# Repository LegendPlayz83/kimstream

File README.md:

# kimstream
This is my Macropad design, which I made from scratch. It has an open top to show to cool pcb designs

# Specifications
 
<ul>
<li>6x Cherry MX Switches <br>
<li>1x XIAO RP2040 <br>
<li>6x Blank DSA Keycaps <br>
<li>4x M3x16 Bolt <br>
<li>4x M3 Heatset <br>
<li>1x EC11 Rotary Encoder</li>  
</ul>

Others:
<ul>
<li>KMK Firmware
<li>Bottom Case.stl
</ul>

<h3>Schematic-</h3>

<h3>PCB</h3>

<h3>Case</h3>

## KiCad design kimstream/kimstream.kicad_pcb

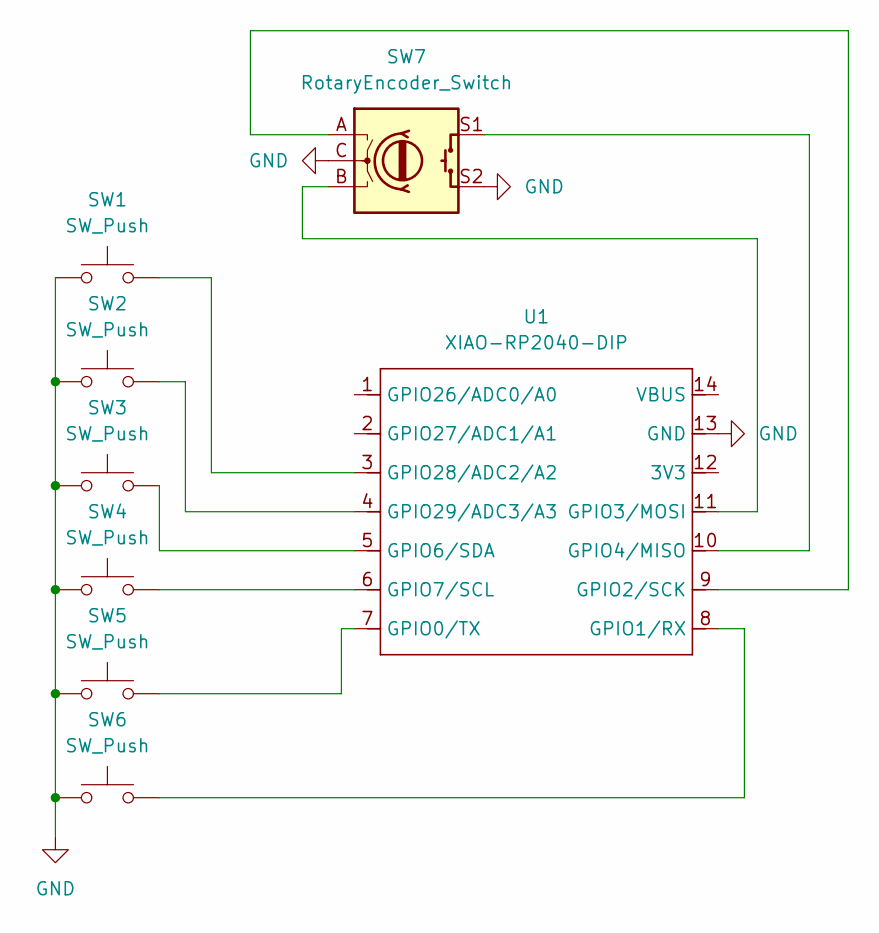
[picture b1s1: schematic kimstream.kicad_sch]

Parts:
SW1, SW2, SW3, SW4, SW5, SW6: SW_Push; SW_Cherry_MX_1.00u_PCB
SW7: RotaryEncoder_Switch; RotaryEncoder_Alps_EC11E-Switch_Vertical_H20mm
U1: XIAO-RP2040-DIP

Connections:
GND: SW1.1, SW2.1, SW3.1, SW4.1, SW5.1, SW6.1, SW7.C, SW7.S2, U1.13 (GND)
unnamed: SW5.2, U1.7 (GPIO0/TX)
unnamed: SW6.2, U1.8 (GPIO1/RX)
unnamed: SW7.A, U1.9 (GPIO2/SCK)
unnamed: SW7.B, U1.11 (GPIO3/MOSI)
unnamed: SW7.S1, U1.10 (GPIO4/MISO)
unnamed: SW3.2, U1.5 (GPIO6/SDA)
unnamed: SW4.2, U1.6 (GPIO7/SCL)
unnamed: SW1.2, U1.3 (GPIO28/ADC2/A2)
unnamed: SW2.2, U1.4 (GPIO29/ADC3/A3)

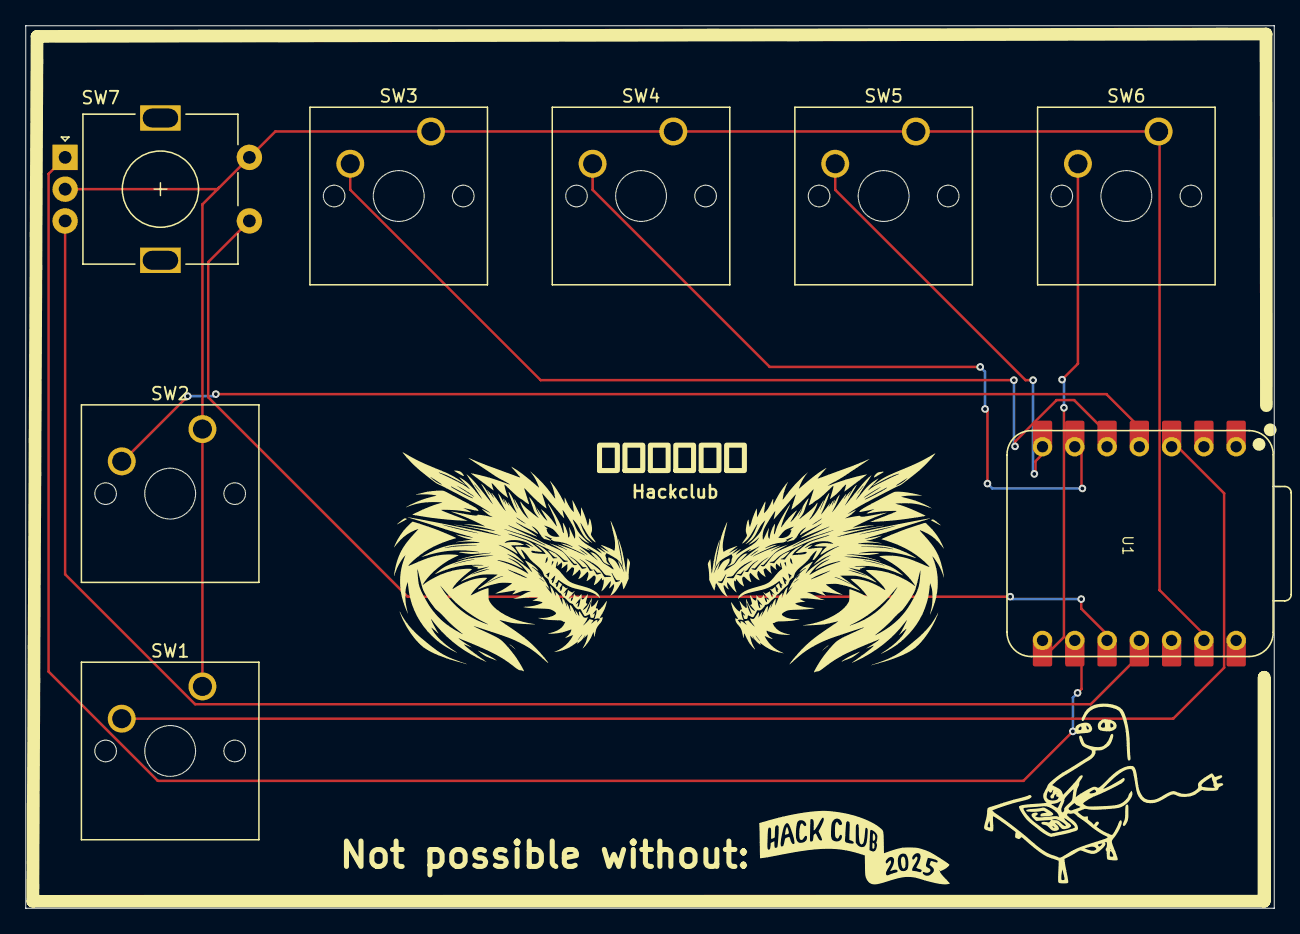
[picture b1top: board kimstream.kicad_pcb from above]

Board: 2 copper layers, 98.2 x 69.5 mm, 8 parts (0 on the bottom side), 10 nets.

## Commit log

2025-09-11 Added all the 3d Models
2025-09-11 gerber file
2025-09-11 uploaded kmk
2025-09-11 Cart
2026-01-14 Update README with additional Macropad design details
    Expanded description of the Macropad design to include details about the open top and PCB visibility.
2026-01-19 Replace old images with new screenshots
    Updated images in README to reflect new screenshots.
